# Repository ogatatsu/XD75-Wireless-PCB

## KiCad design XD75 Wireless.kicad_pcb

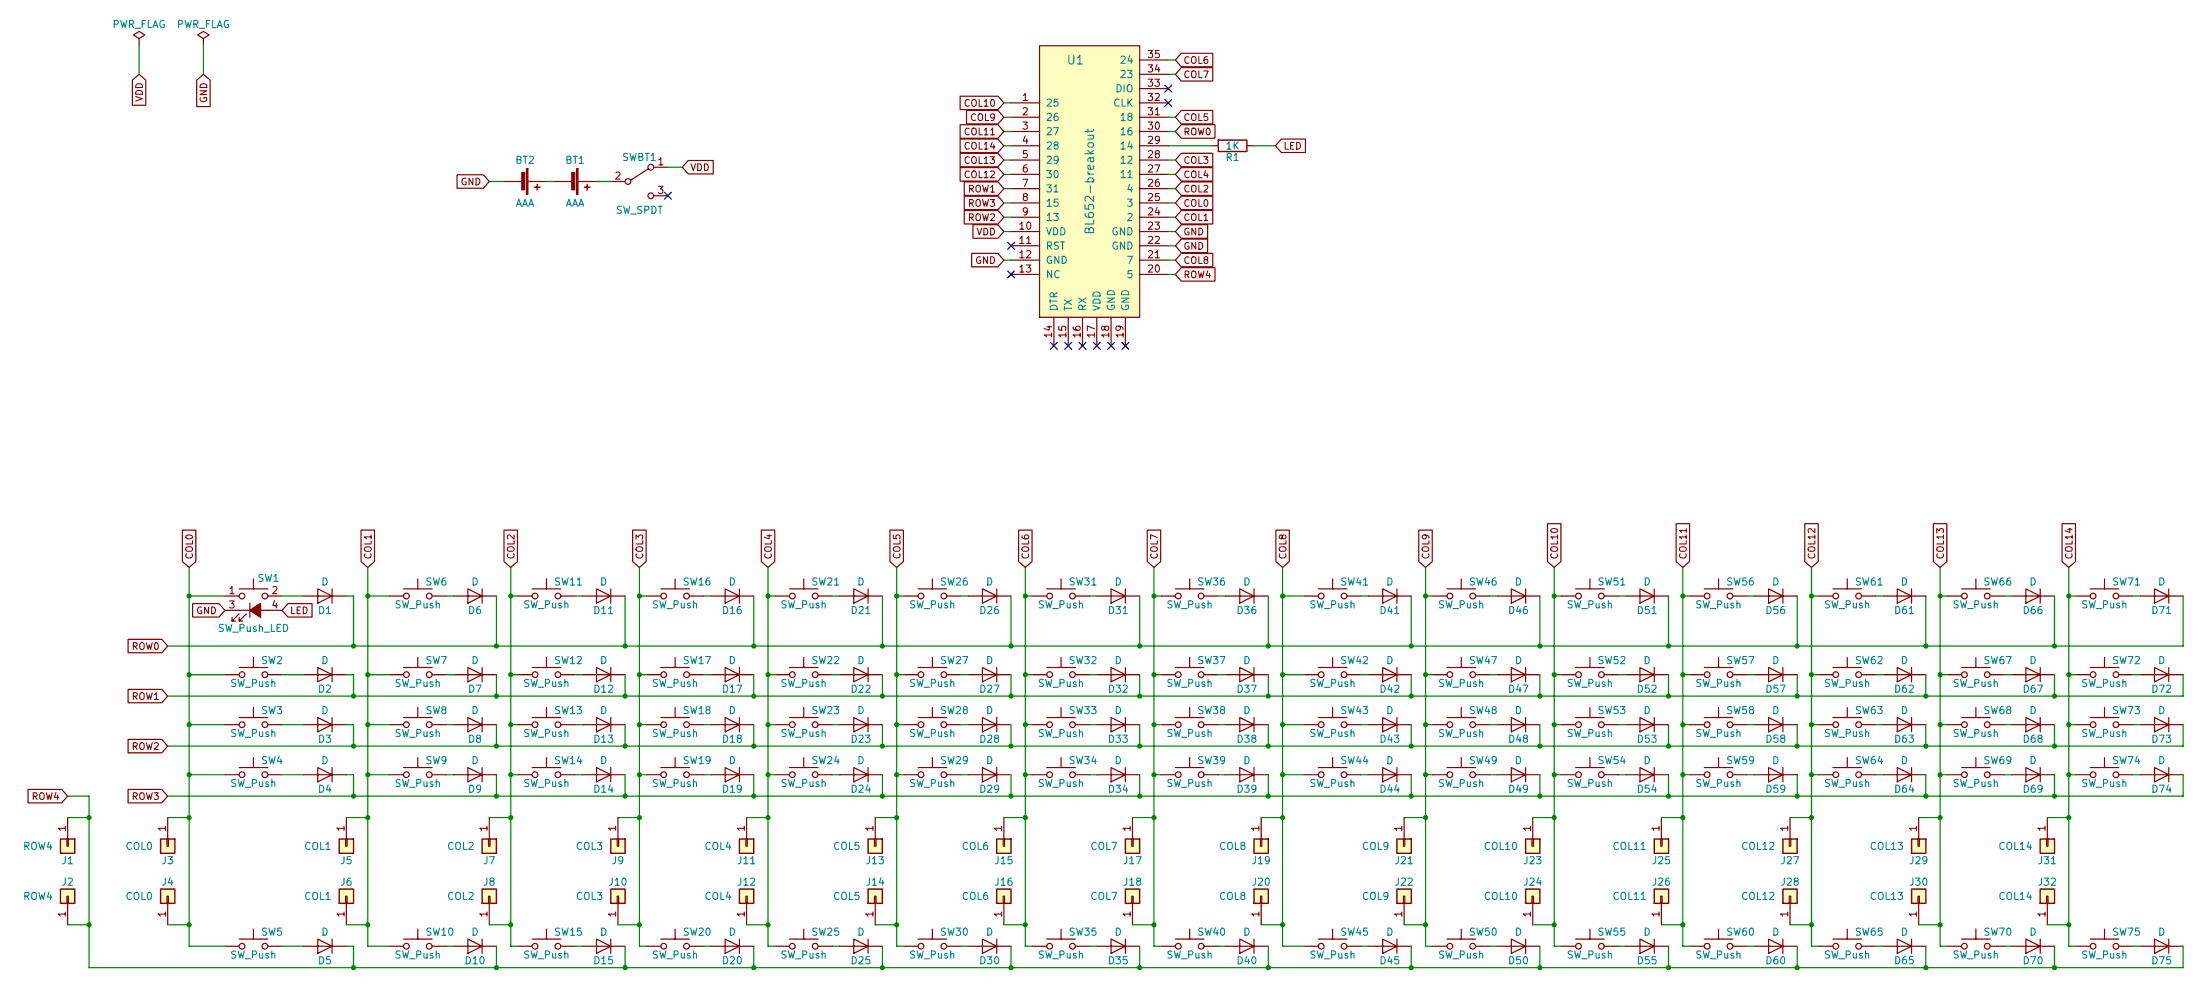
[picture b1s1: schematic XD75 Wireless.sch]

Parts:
BT1, BT2: AAA; BC-0402
D1, D2, D3, D4, D5, D6, D7, D8, D9, D10, D11, D12, D13, D14, D15, D16, D17, D18, D19, D20, D21, D22, D23, D24, D25, D26, D27, D28, D29, D30, D31, D32, D33, D34, D35, D36, D37, D38, D39, D40, D41, D42, D43, D44, D45, D46, D47, D48, D49, D50, D51, D52, D53, D54, D55, D56, D57, D58, D59, D60, D61, D62, D63, D64, D65, D66, D67, D68, D69, D70, D71, D72, D73, D74, D75: D; 1N4148W
J1, J2: ROW4; Wirepad
J3, J4: COL0; Wirepad
J5, J6: COL1; Wirepad
J7, J8: COL2; Wirepad
J9, J10: COL3; Wirepad
J11, J12: COL4; Wirepad
J13, J14: COL5; Wirepad
J15, J16: COL6; Wirepad
J17, J18: COL7; Wirepad
J19, J20: COL8; Wirepad
J21, J22: COL9; Wirepad
J23, J24: COL10; Wirepad
J25, J26: COL11; Wirepad
J27, J28: COL12; Wirepad
J29, J30: COL13; Wirepad
J31, J32: COL14; Wirepad
R1: 1K; 1608
SW1: SW_Push_LED; CherryMx_LED
SW2, SW3, SW4, SW6, SW7, SW8, SW9, SW11, SW12, SW13, SW14, SW16, SW17, SW18, SW19, SW21, SW22, SW23, SW24, SW26, SW27, SW28, SW29, SW31, SW32, SW33, SW34, SW36, SW37, SW38, SW39, SW41, SW42, SW43, SW44, SW46, SW47, SW48, SW49, SW51, SW52, SW53, SW54, SW56, SW57, SW58, SW59, SW61, SW62, SW63, SW64, SW66, SW67, SW68, SW69, SW71, SW72, SW73, SW74: SW_Push; CherryMx
SW5, SW10, SW15, SW20, SW25, SW30, SW35, SW40, SW45, SW50, SW55, SW60, SW65, SW70, SW75: SW_Push; CherryMx_and_KailhLowProfile
SWBT1: SW_SPDT; 5FS1-S1-M6-S-E
U1: BL652-breakout

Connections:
COL0: J3.1, J4.1, SW1.1, SW2.1, SW3.1, SW4.1, SW5.1, U1.25 (3)
COL1: J5.1, J6.1, SW6.1, SW7.1, SW8.1, SW9.1, SW10.1, U1.24 (2)
COL2: J7.1, J8.1, SW11.1, SW12.1, SW13.1, SW14.1, SW15.1, U1.26 (4)
COL3: J9.1, J10.1, SW16.1, SW17.1, SW18.1, SW19.1, SW20.1, U1.28 (12)
COL4: J11.1, J12.1, SW21.1, SW22.1, SW23.1, SW24.1, SW25.1, U1.27 (11)
COL5: J13.1, J14.1, SW26.1, SW27.1, SW28.1, SW29.1, SW30.1, U1.31 (18)
COL6: J15.1, J16.1, SW31.1, SW32.1, SW33.1, SW34.1, SW35.1, U1.35 (24)
COL7: J17.1, J18.1, SW36.1, SW37.1, SW38.1, SW39.1, SW40.1, U1.34 (23)
COL8: J19.1, J20.1, SW41.1, SW42.1, SW43.1, SW44.1, SW45.1, U1.21 (7)
COL9: J21.1, J22.1, SW46.1, SW47.1, SW48.1, SW49.1, SW50.1, U1.2 (26)
COL10: J23.1, J24.1, SW51.1, SW52.1, SW53.1, SW54.1, SW55.1, U1.1 (25)
COL11: J25.1, J26.1, SW56.1, SW57.1, SW58.1, SW59.1, SW60.1, U1.3 (27)
COL12: J27.1, J28.1, SW61.1, SW62.1, SW63.1, SW64.1, SW65.1, U1.6 (30)
COL13: J29.1, J30.1, SW66.1, SW67.1, SW68.1, SW69.1, SW70.1, U1.5 (29)
COL14: J31.1, J32.1, SW71.1, SW72.1, SW73.1, SW74.1, SW75.1, U1.4 (28)
GND: BT2.2 (-), SW1.3 (K), U1.12 (GND), U1.22 (GND), U1.23 (GND)
LED: R1.1, SW1.4 (A)
unnamed: BT1.1 (+), SWBT1.2 (B)
unnamed: BT1.2 (-), BT2.1 (+)
unnamed: D1.2 (A), SW1.2
unnamed: D2.2 (A), SW2.2
unnamed: D3.2 (A), SW3.2
unnamed: D4.2 (A), SW4.2
unnamed: D5.2 (A), SW5.2
unnamed: D6.2 (A), SW6.2
unnamed: D7.2 (A), SW7.2
unnamed: D8.2 (A), SW8.2
unnamed: D9.2 (A), SW9.2
unnamed: D10.2 (A), SW10.2
unnamed: D11.2 (A), SW11.2
unnamed: D12.2 (A), SW12.2
unnamed: D13.2 (A), SW13.2
unnamed: D14.2 (A), SW14.2
unnamed: D15.2 (A), SW15.2
unnamed: D16.2 (A), SW16.2
unnamed: D17.2 (A), SW17.2
unnamed: D18.2 (A), SW18.2
unnamed: D19.2 (A), SW19.2
unnamed: D20.2 (A), SW20.2
unnamed: D21.2 (A), SW21.2
unnamed: D22.2 (A), SW22.2
unnamed: D23.2 (A), SW23.2
unnamed: D24.2 (A), SW24.2
unnamed: D25.2 (A), SW25.2
unnamed: D26.2 (A), SW26.2
unnamed: D27.2 (A), SW27.2
unnamed: D28.2 (A), SW28.2
unnamed: D29.2 (A), SW29.2
unnamed: D30.2 (A), SW30.2
unnamed: D31.2 (A), SW31.2
unnamed: D32.2 (A), SW32.2
unnamed: D33.2 (A), SW33.2
unnamed: D34.2 (A), SW34.2
unnamed: D35.2 (A), SW35.2
unnamed: D36.2 (A), SW36.2
unnamed: D37.2 (A), SW37.2
unnamed: D38.2 (A), SW38.2
unnamed: D39.2 (A), SW39.2
unnamed: D40.2 (A), SW40.2
unnamed: D41.2 (A), SW41.2
unnamed: D42.2 (A), SW42.2
unnamed: D43.2 (A), SW43.2
unnamed: D44.2 (A), SW44.2
unnamed: D45.2 (A), SW45.2
unnamed: D46.2 (A), SW46.2
unnamed: D47.2 (A), SW47.2
unnamed: D48.2 (A), SW48.2
unnamed: D49.2 (A), SW49.2
unnamed: D50.2 (A), SW50.2
unnamed: D51.2 (A), SW51.2
unnamed: D52.2 (A), SW52.2
unnamed: D53.2 (A), SW53.2
unnamed: D54.2 (A), SW54.2
unnamed: D55.2 (A), SW55.2
unnamed: D56.2 (A), SW56.2
unnamed: D57.2 (A), SW57.2
unnamed: D58.2 (A), SW58.2
unnamed: D59.2 (A), SW59.2
unnamed: D60.2 (A), SW60.2
unnamed: D61.2 (A), SW61.2
unnamed: D62.2 (A), SW62.2
unnamed: D63.2 (A), SW63.2
unnamed: D64.2 (A), SW64.2
unnamed: D65.2 (A), SW65.2
unnamed: D66.2 (A), SW66.2
unnamed: D67.2 (A), SW67.2
unnamed: D68.2 (A), SW68.2
unnamed: D69.2 (A), SW69.2
unnamed: D70.2 (A), SW70.2
unnamed: D71.2 (A), SW71.2
unnamed: D72.2 (A), SW72.2
unnamed: D73.2 (A), SW73.2
unnamed: D74.2 (A), SW74.2
unnamed: D75.2 (A), SW75.2
unnamed: R1.2, U1.29 (14)
ROW0: D1.1 (K), D6.1 (K), D11.1 (K), D16.1 (K), D21.1 (K), D26.1 (K), D31.1 (K), D36.1 (K), D41.1 (K), D46.1 (K), D51.1 (K), D56.1 (K), D61.1 (K), D66.1 (K), D71.1 (K), U1.30 (16)
ROW1: D2.1 (K), D7.1 (K), D12.1 (K), D17.1 (K), D22.1 (K), D27.1 (K), D32.1 (K), D37.1 (K), D42.1 (K), D47.1 (K), D52.1 (K), D57.1 (K), D62.1 (K), D67.1 (K), D72.1 (K), U1.7 (31)
ROW2: D3.1 (K), D8.1 (K), D13.1 (K), D18.1 (K), D23.1 (K), D28.1 (K), D33.1 (K), D38.1 (K), D43.1 (K), D48.1 (K), D53.1 (K), D58.1 (K), D63.1 (K), D68.1 (K), D73.1 (K), U1.9 (13)
ROW3: D4.1 (K), D9.1 (K), D14.1 (K), D19.1 (K), D24.1 (K), D29.1 (K), D34.1 (K), D39.1 (K), D44.1 (K), D49.1 (K), D54.1 (K), D59.1 (K), D64.1 (K), D69.1 (K), D74.1 (K), U1.8 (15)
ROW4: D5.1 (K), D10.1 (K), D15.1 (K), D20.1 (K), D25.1 (K), D30.1 (K), D35.1 (K), D40.1 (K), D45.1 (K), D50.1 (K), D55.1 (K), D60.1 (K), D65.1 (K), D70.1 (K), D75.1 (K), J1.1, J2.1, U1.20 (5)
VDD: SWBT1.1 (A), U1.10 (VDD)

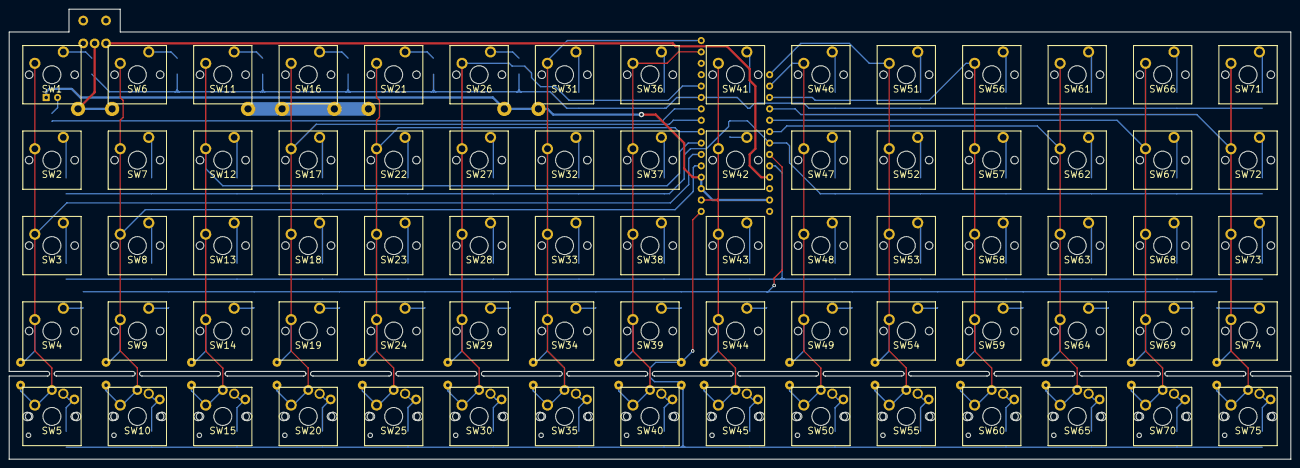
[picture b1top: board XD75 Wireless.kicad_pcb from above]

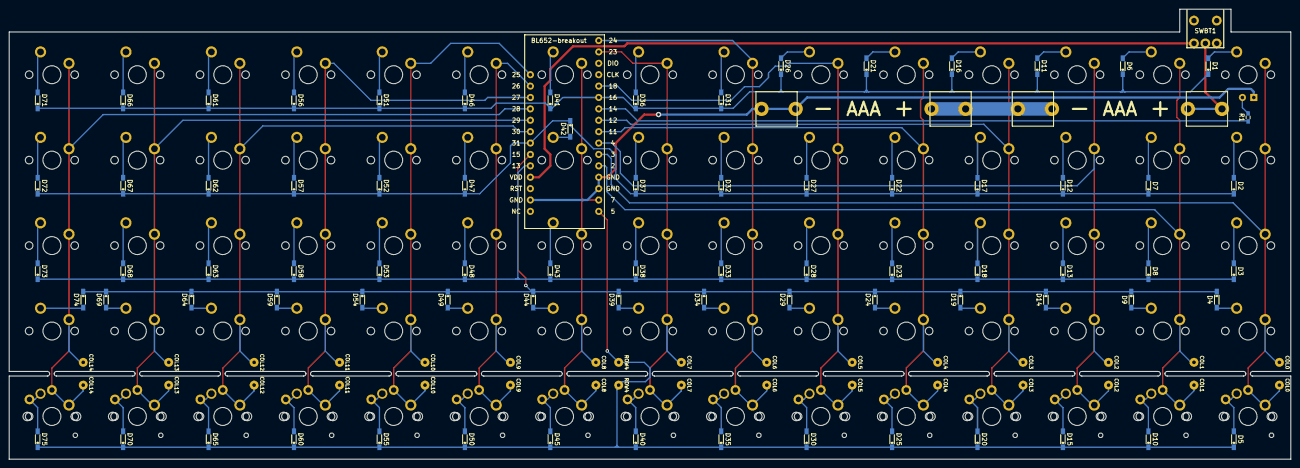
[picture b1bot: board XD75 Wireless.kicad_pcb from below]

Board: 2 copper layers, 285.8 x 100.3 mm, 187 parts (112 on the bottom side), 101 nets.
